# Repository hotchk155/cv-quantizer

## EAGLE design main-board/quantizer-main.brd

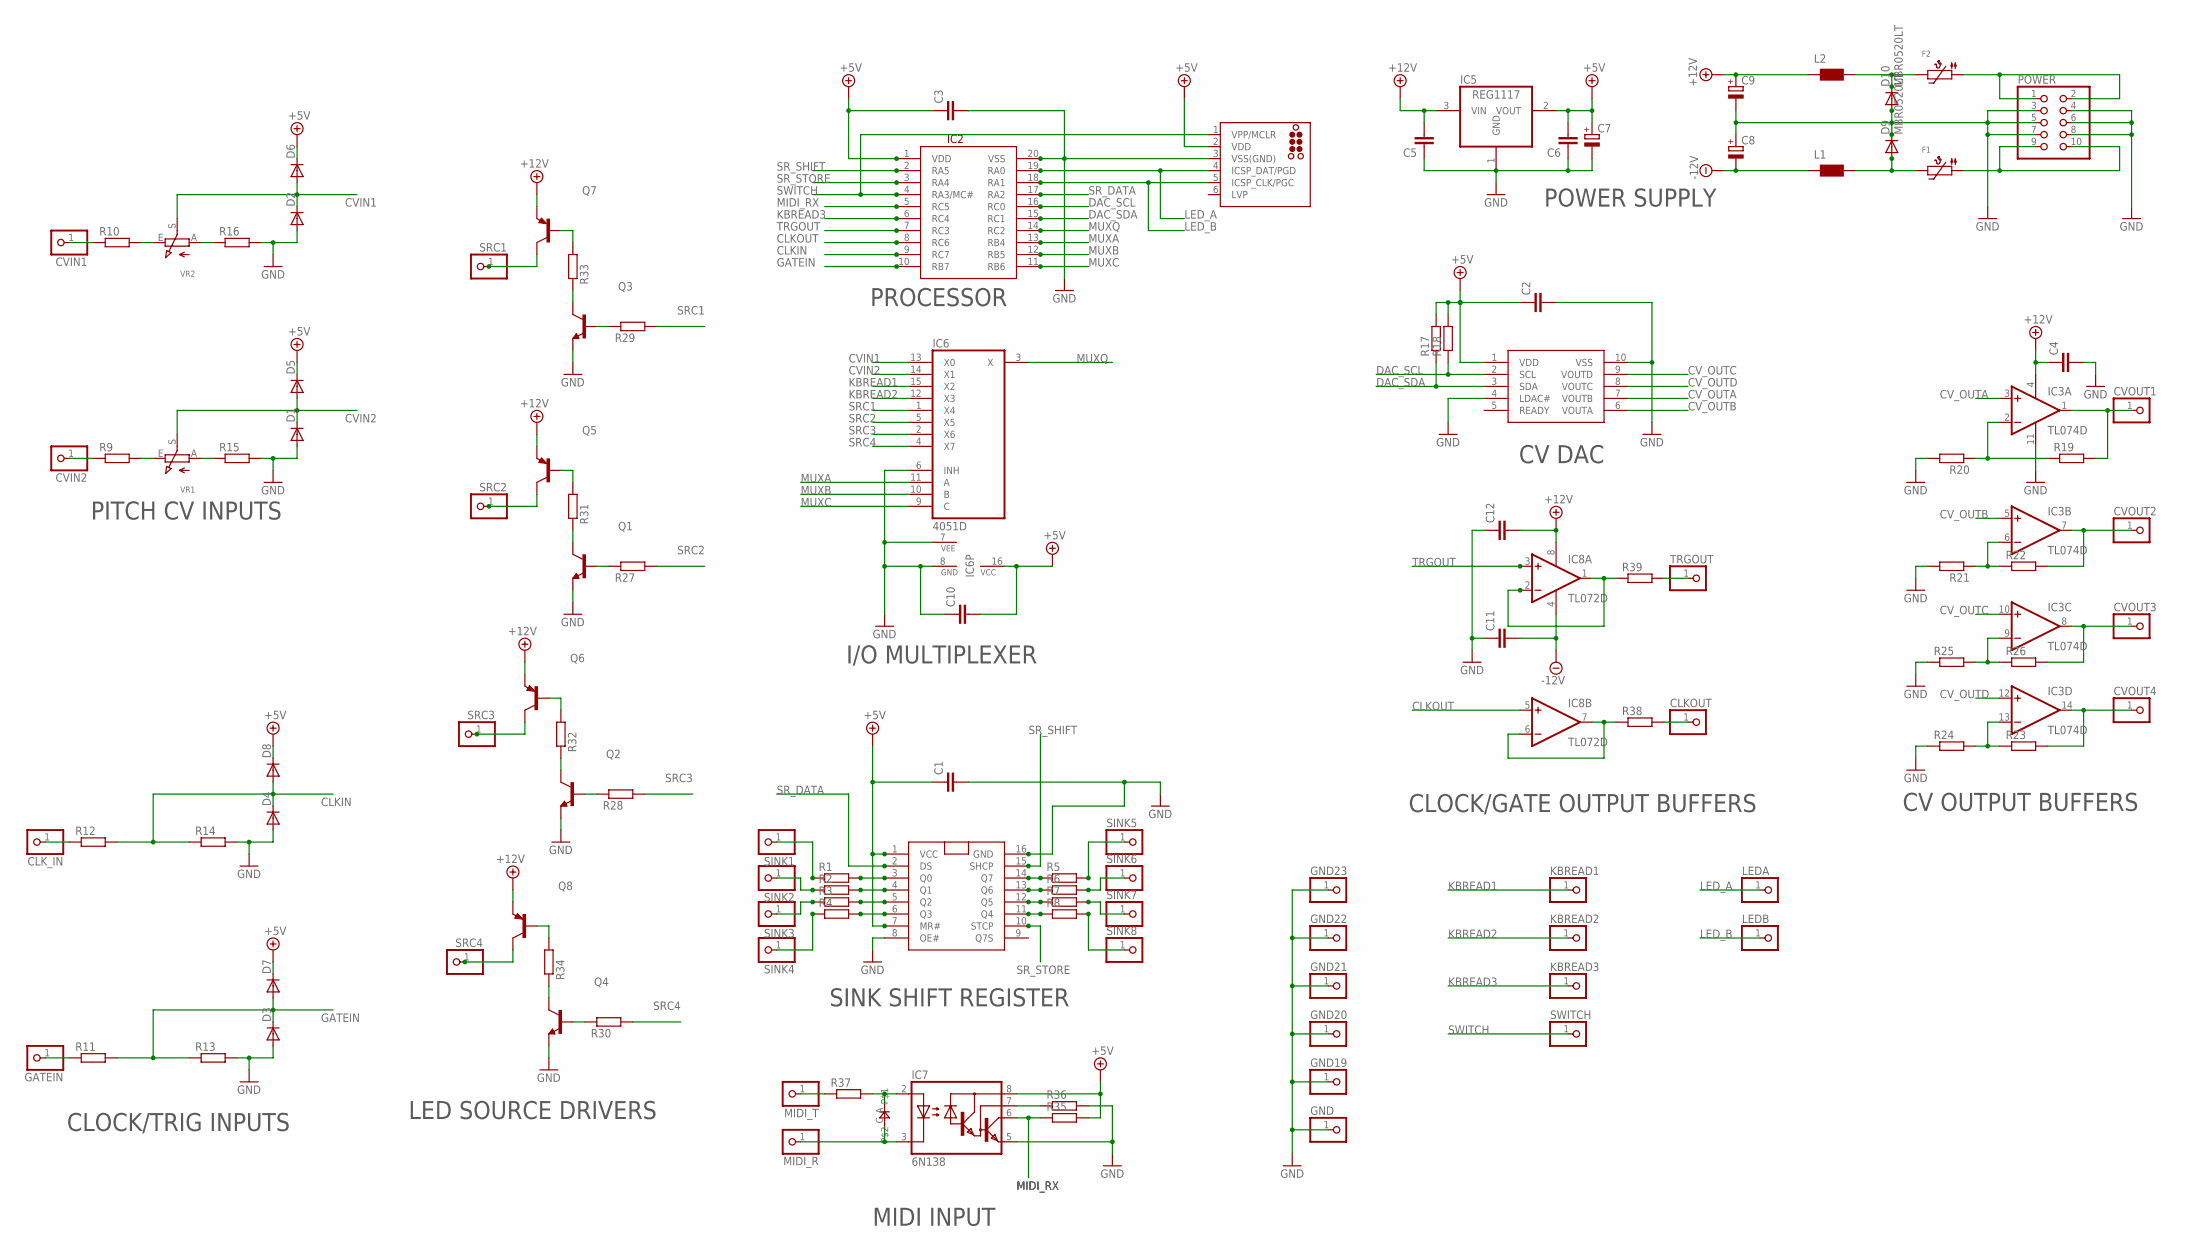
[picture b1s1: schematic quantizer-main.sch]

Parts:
C1, C2, C3, C4, C5, C6, C10, C11, C12: C-EUC0805; C0805
C7: CPOL-EUE2.5-5; E2,5-5
C8, C9: CPOL-EUE2.5-7; E2,5-7
CLKOUT: PINHD-1X1; 1X01
CLK_IN: PINHD-1X1; 1X01
CVIN1, CVIN2: PINHD-1X1; 1X01
CVOUT1, CVOUT2, CVOUT3, CVOUT4: PINHD-1X1; 1X01
D1, D2, D3, D4, D5, D6, D7, D8: DIODE-SOD123; SOD123
D9, D10: MBR0520LT; SOD123
D11: 0805DIODE
F1, F2: PTC1210
GATEIN: PINHD-1X1; 1X01
GND, GND19, GND20, GND21, GND22, GND23: PINHD-1X1; 1X01
IC1: NPIC6C596; SO16
IC2: PIC16F1829SOIC; SO20W
IC3: TL074D; SO14
IC4: MCP4728_QUAD_DAC; MSOP10
IC5: REG1117; SOT223
IC6: 4051D; SO16
IC7: 6N138; DIL08
IC8: TL072D; SO08
J1: TC2030-MCP-NL
KBREAD1, KBREAD2, KBREAD3: PINHD-1X1; 1X01
L1, L2: WE-CBF_0805; 0805
LEDA: PINHD-1X1; 1X01
LEDB: PINHD-1X1; 1X01
MIDI_R: PINHD-1X1; 1X01
MIDI_T: PINHD-1X1; 1X01
POWER: PINHD-2X5; 2X05
Q1, Q2, Q3, Q4: MMBT3904LT1-NPN-SOT23-BEC; SOT23-BEC
Q5, Q6, Q7, Q8: MMBT3906LT1-PNP-SOT23-BEC; SOT23-BEC
R1, R2, R3, R4, R5, R6, R7, R8, R9, R10, R11, R12, R13, R14, R15, R16, R17, R18, R19, R20, R21, R22, R23, R24, R25, R26, R27, R28, R29, R30, R31, R32, R33, R34, R35, R36, R37, R38, R39: R-EU_R0805; R0805
SINK1, SINK2, SINK3, SINK4, SINK5, SINK6, SINK7, SINK8: PINHD-1X1; 1X01
SRC1, SRC2, SRC3, SRC4: PINHD-1X1; 1X01
SWITCH: PINHD-1X1; 1X01
TRGOUT: PINHD-1X1; 1X01
VR1, VR2: TRIMPOT10K_BOURNS; TRIMPOT_BOURNS3MM

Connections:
+5V: C1.1, C2.1, C3.1, C6.2, C7.+, C10.2, D5.C, D6.C, D7.C, D8.C, IC1.1 (VCC), IC1.7 (MR#), IC2.1 (VDD), IC4.1 (VDD), IC5.2 (VOUT), IC6.16 (VCC), IC7.8 (VCC), J1.2 (VDD), R17.2, R18.2, R35.2
+12V: C4.1, C5.2, C9.+, C12.2, IC3.4 (V+), IC5.3 (VIN), IC8.8 (V+), L2.1, Q5.E, Q6.E, Q7.E, Q8.E
-12V: C8.-, C11.2, IC8.4 (V-), L1.1
CLKIN: D4.C, D8.A, IC2.9 (RC7), R12.2, R14.1
CLKOUT: IC2.8 (RC6), IC8.5 (+IN)
CVIN1: D2.C, D6.A, IC6.13 (X0), VR2.S
CVIN2: D1.C, D5.A, IC6.14 (X1), VR1.S
CV_OUTA: IC3.3 (+IN), IC4.7 (VOUTB)
CV_OUTB: IC3.5 (+IN), IC4.6 (VOUTA)
CV_OUTC: IC3.10 (+IN), IC4.9 (VOUTD)
CV_OUTD: IC3.12 (+IN), IC4.8 (VOUTC)
DAC_SCL: IC2.16 (RC0), IC4.2 (SCL), R18.1
DAC_SDA: IC2.15 (RC1), IC4.3 (SDA), R17.1
GATEIN: D3.C, D7.A, IC2.10 (RB7), R11.2, R13.1
GND: C1.2, C2.2, C3.2, C4.2, C5.1, C6.1, C7.-, C8.+, C9.-, C10.1, C11.1, C12.1, D1.A, D2.A, D3.A, D4.A, D9.C, D10.A, GND.1, GND19.1, GND20.1, GND21.1, GND22.1, GND23.1, IC1.8 (OE#), IC1.16 (GND), IC2.20 (VSS), IC3.11 (V-), IC4.4 (LDAC#), IC4.10 (VSS), IC5.1 (GND), IC6.6 (INH), IC6.7 (VEE), IC6.8 (GND), IC7.5 (GND), J1.3 (VSS(GND)), POWER.3, POWER.4, POWER.5, POWER.6, POWER.7, POWER.8, Q1.E, Q2.E, Q3.E, Q4.E, R13.2, R14.2, R15.2, R16.2, R20.2, R21.2, R24.1, R25.1, R36.2
KBREAD1: IC6.15 (X2), KBREAD1.1
KBREAD2: IC6.12 (X3), KBREAD2.1
KBREAD3: IC2.6 (RC4), KBREAD3.1
LED_A: IC2.19 (RA0), J1.4 (ICSP_DAT/PGD), LEDA.1
LED_B: IC2.18 (RA1), J1.5 (ICSP_CLK/PGC), LEDB.1
MIDI_RX: IC2.5 (RC5), IC7.6 (VO), R35.1
MUXA: IC2.13 (RB4), IC6.11 (A)
MUXB: IC2.12 (RB5), IC6.10 (B)
MUXC: IC2.11 (RB6), IC6.9 (C)
MUXQ: IC2.14 (RC2), IC6.3 (X)
unnamed: CVOUT1.1, IC3.1 (OUT), R19.2
unnamed: IC3.2 (-IN), R19.1, R20.1
unnamed: R1.1, SINK1.1
unnamed: IC3.6 (-IN), R21.1, R22.1
unnamed: CVOUT2.1, IC3.7 (OUT), R22.2
unnamed: R2.1, SINK2.1
unnamed: R3.1, SINK3.1
unnamed: R4.1, SINK4.1
unnamed: CVOUT3.1, IC3.8 (OUT), R26.2
unnamed: CVOUT4.1, IC3.14 (OUT), R23.2
unnamed: IC3.9 (-IN), R25.2, R26.1
unnamed: IC3.13 (-IN), R23.1, R24.2
unnamed: IC1.3 (Q0), R1.2
unnamed: IC1.4 (Q1), R2.2
unnamed: IC1.5 (Q2), R3.2
unnamed: IC1.6 (Q3), R4.2
unnamed: R5.2, SINK5.1
unnamed: R6.2, SINK6.1
unnamed: R7.2, SINK7.1
unnamed: R8.2, SINK8.1
unnamed: IC1.14 (Q7), R5.1
unnamed: IC1.13 (Q6), R6.1
unnamed: IC1.12 (Q5), R7.1
unnamed: IC1.11 (Q4), R8.1
unnamed: Q7.C, SRC1.1
unnamed: Q3.B, R29.1
unnamed: MIDI_T.1, R37.1
unnamed: Q7.B, R33.2
unnamed: Q5.C, SRC2.1
unnamed: Q1.B, R27.1
unnamed: D11.A, IC7.2 (A), R37.2
unnamed: Q3.C, R33.1
unnamed: Q5.B, R31.2
unnamed: Q1.C, R31.1
unnamed: D11.C, IC7.3 (C), MIDI_R.1
unnamed: Q6.C, SRC3.1
unnamed: Q2.B, R28.1
unnamed: Q6.B, R32.2
unnamed: Q2.C, R32.1
unnamed: Q8.C, SRC4.1
unnamed: D10.C, F2.P$2 (2), L2.2
unnamed: D9.A, F1.P$2 (2), L1.2
unnamed: Q4.B, R30.1
unnamed: Q8.B, R34.2
unnamed: CLK_IN.1, R12.1
unnamed: IC7.7 (VB), R36.1
unnamed: Q4.C, R34.1
unnamed: GATEIN.1, R11.1
unnamed: CVIN2.1, R9.1
unnamed: R9.2, VR1.E
unnamed: R15.1, VR1.A
unnamed: CVIN1.1, R10.1
unnamed: R10.2, VR2.E
unnamed: R16.1, VR2.A
unnamed: IC8.1 (OUT), IC8.2 (-IN), R39.1
unnamed: IC8.6 (-IN), IC8.7 (OUT), R38.1
unnamed: F1.P$1 (1), POWER.9, POWER.10
unnamed: R39.2, TRGOUT.1
unnamed: CLKOUT.1, R38.2
unnamed: F2.P$1 (1), POWER.1, POWER.2
SRC1: IC6.1 (X4), R29.2
SRC2: IC6.5 (X5), R27.2
SRC3: IC6.2 (X6), R28.2
SRC4: IC6.4 (X7), R30.2
SR_DATA: IC1.2 (DS), IC2.17 (RA2)
SR_SHIFT: IC1.15 (SHCP), IC2.2 (RA5)
SR_STORE: IC1.10 (STCP), IC2.3 (RA4)
SWITCH: IC2.4 (RA3/MC#), J1.1 (VPP/MCLR), SWITCH.1
TRGOUT: IC2.7 (RC3), IC8.3 (+IN)

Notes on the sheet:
MIDI INPUT
POWER SUPPLY
CV OUTPUT BUFFERS
CV DAC
CLOCK/GATE OUTPUT BUFFERS
PROCESSOR
I/O MULTIPLEXER
SINK SHIFT REGISTER
CLOCK/TRIG INPUTS
LED SOURCE DRIVERS
PITCH CV INPUTS

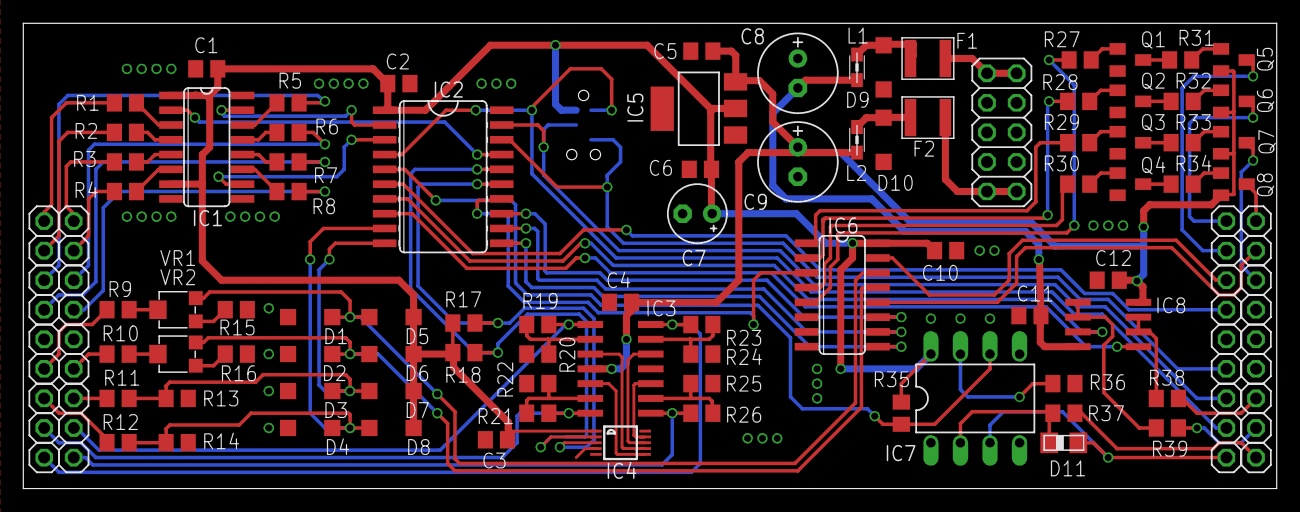
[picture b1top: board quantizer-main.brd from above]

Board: 2 copper layers, 107.7 x 40.0 mm, 122 parts (1 on the bottom side), 94 nets.

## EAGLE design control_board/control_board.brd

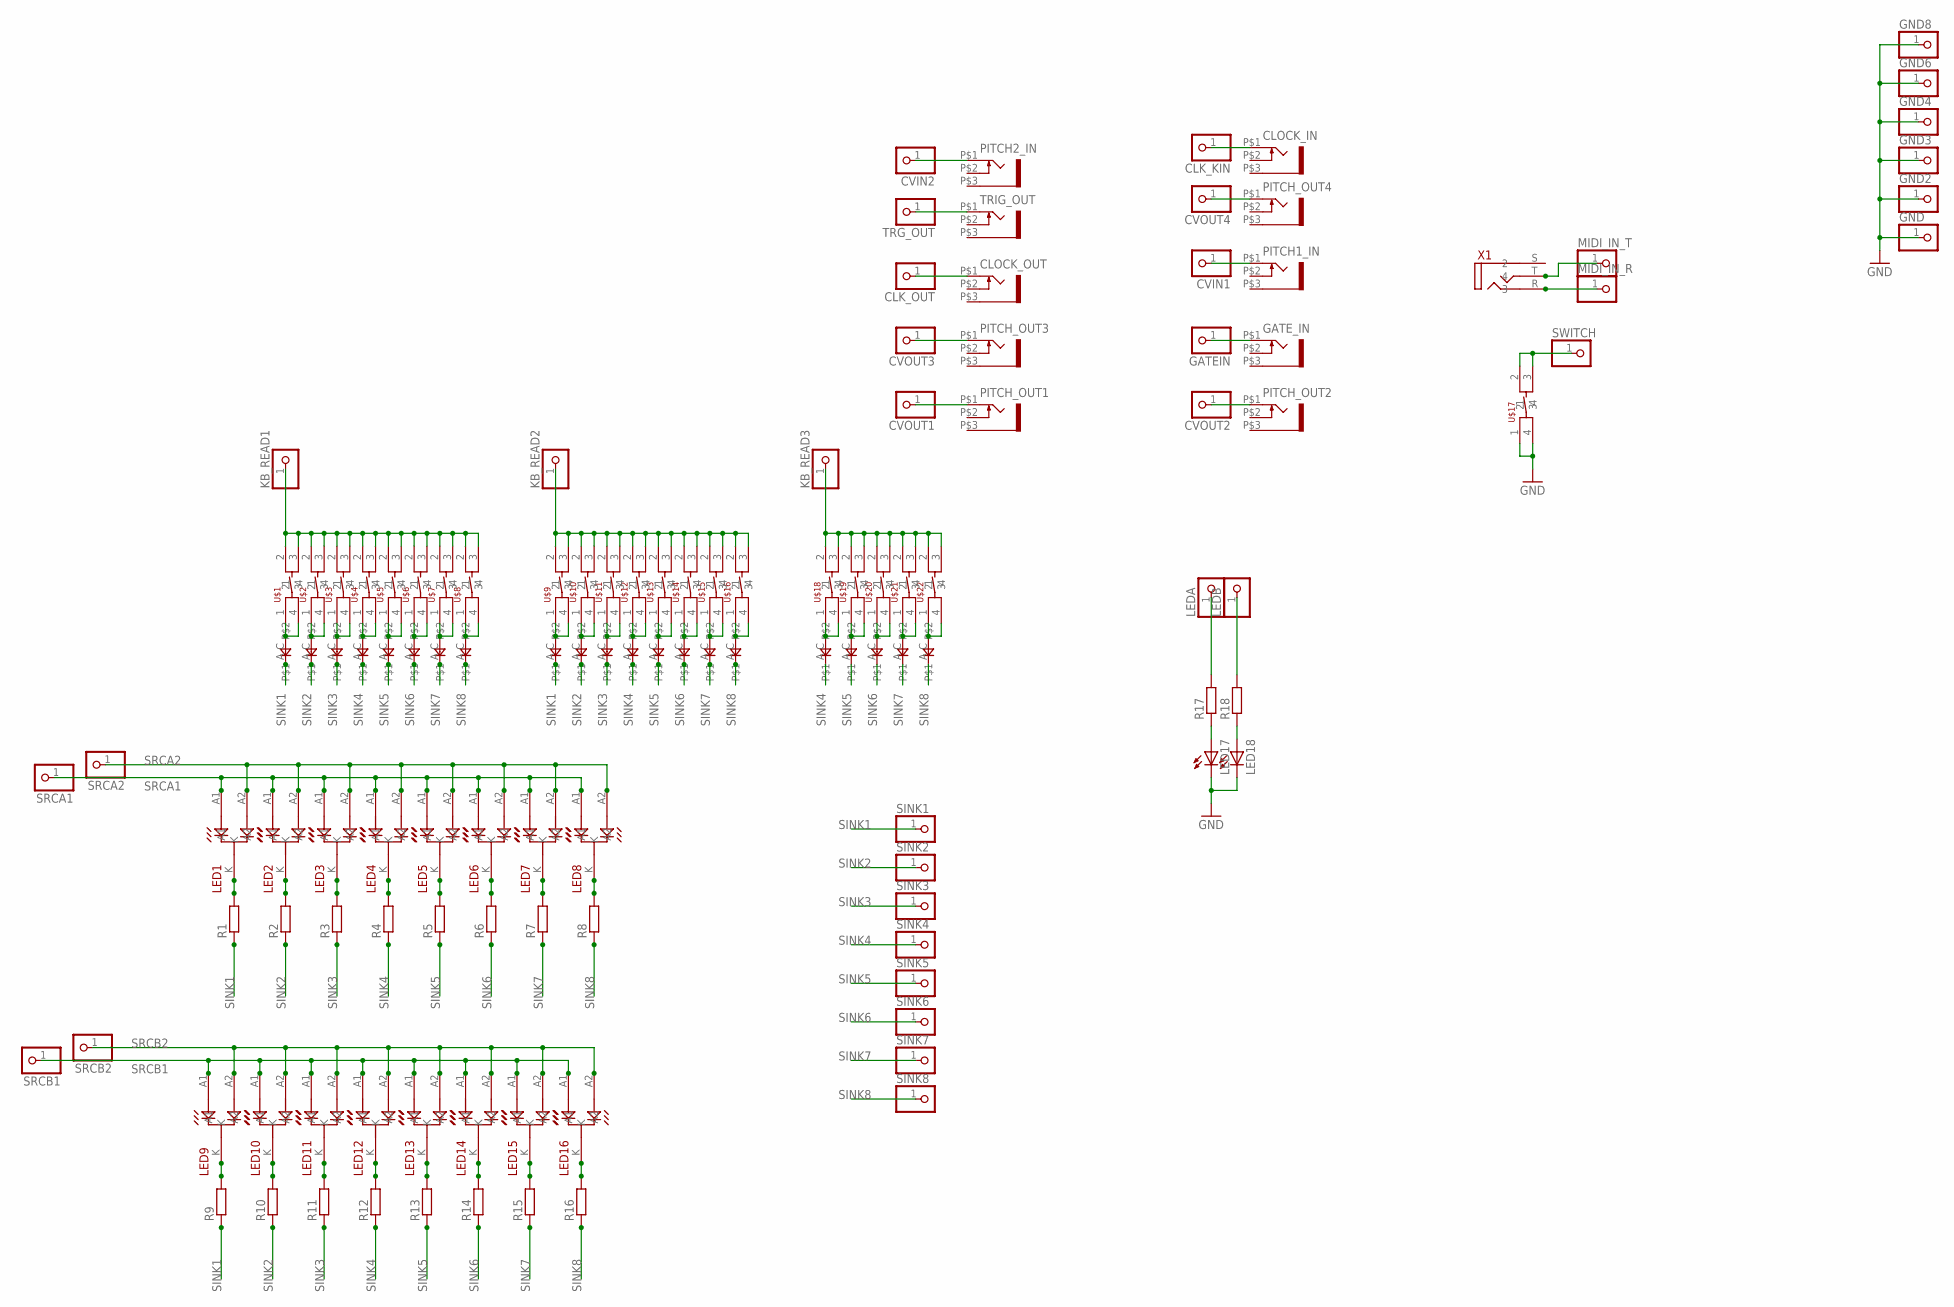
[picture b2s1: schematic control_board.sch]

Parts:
CLK_KIN: PINHD-1X1; 1X01
CLK_OUT: PINHD-1X1; 1X01
CLOCK_IN: WQP-PJ301M-12_JACK
CLOCK_OUT: WQP-PJ301M-12_JACK
CVIN1, CVIN2: PINHD-1X1; 1X01
CVOUT1, CVOUT2, CVOUT3, CVOUT4: PINHD-1X1; 1X01
GATEIN: PINHD-1X1; 1X01
GATE_IN: WQP-PJ301M-12_JACK
GND, GND2, GND3, GND4, GND6, GND8: PINHD-1X1; 1X01
KB_READ1, KB_READ2, KB_READ3: PINHD-1X1; 1X01
LED1, LED2, LED3, LED4, LED5, LED6, LED7, LED8, LED9, LED10, LED11, LED12, LED13, LED14, LED15, LED16: BICOL_LED_CC
LED17, LED18: LED3MM
LEDA: PINHD-1X1; 1X01
LEDB: PINHD-1X1; 1X01
MIDI_IN_R: PINHD-1X1; 1X01
MIDI_IN_T: PINHD-1X1; 1X01
PITCH1_IN, PITCH2_IN: WQP-PJ301M-12_JACK
PITCH_OUT1, PITCH_OUT2, PITCH_OUT3, PITCH_OUT4: WQP-PJ301M-12_JACK
R1, R2, R3, R4, R5, R6, R7, R8, R9, R10, R11, R12, R13, R14, R15, R16, R17, R18: R-EU_R0805; R0805
SINK1, SINK2, SINK3, SINK4, SINK5, SINK6, SINK7, SINK8: PINHD-1X1; 1X01
SRCA1, SRCA2: PINHD-1X1; 1X01
SRCB1, SRCB2: PINHD-1X1; 1X01
SWITCH: PINHD-1X1; 1X01
TRG_OUT: PINHD-1X1; 1X01
TRIG_OUT: WQP-PJ301M-12_JACK
U$1, U$2, U$3, U$4, U$5, U$6, U$7, U$8, U$9, U$10, U$11, U$12, U$13, U$14, U$15, U$16, U$17, U$18, U$19, U$20, U$21, U$22: 6MM_TACT; 6MMTACT
U$23, U$24, U$25, U$26, U$27, U$28, U$29, U$30, U$31, U$32, U$33, U$34, U$35, U$36, U$37, U$38, U$39, U$40, U$41, U$42, U$43: 0805DIODE
X1: VERTICAL_3_5MM_SOCKETTHONK; PJ301CM

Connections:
GND: GND.1, GND2.1, GND3.1, GND4.1, GND6.1, GND8.1, LED17.K (C), LED18.K (C), U$17.1, U$17.4
KB_READ: KB_READ2.1, U$9.2, U$9.3, U$10.2, U$10.3, U$11.2, U$11.3, U$12.2, U$12.3, U$13.2, U$13.3, U$14.2, U$14.3, U$15.2, U$15.3, U$16.2, U$16.3
LED2: LED2.K, R2.2
LEDA: LEDA.1, R17.2
unnamed: U$9.1, U$9.4, U$31.C
unnamed: KB_READ1.1, U$1.2, U$1.3, U$2.2, U$2.3, U$3.2, U$3.3, U$4.2, U$4.3, U$5.2, U$5.3, U$6.2, U$6.3, U$7.2, U$7.3, U$8.2, U$8.3
unnamed: U$10.1, U$10.4, U$32.C
unnamed: U$1.1, U$1.4, U$23.C
unnamed: U$2.1, U$2.4, U$24.C
unnamed: U$3.1, U$3.4, U$25.C
unnamed: U$4.1, U$4.4, U$26.C
unnamed: U$5.1, U$5.4, U$27.C
unnamed: U$18.1, U$18.4, U$39.C
unnamed: U$19.1, U$19.4, U$40.C
unnamed: U$20.1, U$20.4, U$41.C
unnamed: KB_READ3.1, U$18.2, U$18.3, U$19.2, U$19.3, U$20.2, U$20.3, U$21.2, U$21.3, U$22.2, U$22.3
unnamed: U$6.1, U$6.4, U$28.C
unnamed: U$11.1, U$11.4, U$33.C
unnamed: U$12.1, U$12.4, U$34.C
unnamed: U$13.1, U$13.4, U$35.C
unnamed: LED1.K, R1.2
unnamed: U$14.1, U$14.4, U$36.C
unnamed: LED17.A, R17.1
unnamed: LED3.K, R3.2
unnamed: LED4.K, R4.2
unnamed: LED5.K, R5.2
unnamed: LED6.K, R6.2
unnamed: LED7.K, R7.2
unnamed: LED8.K, R8.2
unnamed: U$16.1, U$16.4, U$38.C
unnamed: LED9.K, R9.2
unnamed: U$15.1, U$15.4, U$37.C
unnamed: LED10.K, R10.2
unnamed: LED11.K, R11.2
unnamed: LED12.K, R12.2
unnamed: LED13.K, R13.2
unnamed: LED14.K, R14.2
unnamed: LED15.K, R15.2
unnamed: LED16.K, R16.2
unnamed: LED18.A, R18.1
unnamed: MIDI_IN_R.1, X1.R (3)
unnamed: U$8.1, U$8.4, U$30.C
unnamed: U$7.1, U$7.4, U$29.C
unnamed: LEDB.1, R18.2
unnamed: U$22.1, U$22.4, U$43.C
unnamed: U$21.1, U$21.4, U$42.C
unnamed: SWITCH.1, U$17.2, U$17.3
unnamed: MIDI_IN_T.1, X1.T (4)
unnamed: CVIN2.1, PITCH2_IN.P$1 (2)
unnamed: TRG_OUT.1, TRIG_OUT.P$1 (2)
unnamed: CLK_OUT.1, CLOCK_OUT.P$1 (2)
unnamed: CVOUT3.1, PITCH_OUT3.P$1 (2)
unnamed: CVOUT1.1, PITCH_OUT1.P$1 (2)
unnamed: CLK_KIN.1, CLOCK_IN.P$1 (2)
unnamed: CVOUT4.1, PITCH_OUT4.P$1 (2)
unnamed: CVIN1.1, PITCH1_IN.P$1 (2)
unnamed: GATEIN.1, GATE_IN.P$1 (2)
unnamed: CVOUT2.1, PITCH_OUT2.P$1 (2)
SINK1: R1.1, R9.1, SINK1.1, U$23.A, U$31.A
SINK2: R2.1, R10.1, SINK2.1, U$24.A, U$32.A
SINK3: R3.1, R11.1, SINK3.1, U$25.A, U$33.A
SINK4: R4.1, R12.1, SINK4.1, U$26.A, U$34.A, U$39.A
SINK5: R5.1, R13.1, SINK5.1, U$27.A, U$35.A, U$40.A
SINK6: R6.1, R14.1, SINK6.1, U$28.A, U$36.A, U$41.A
SINK7: R7.1, R15.1, SINK7.1, U$29.A, U$37.A, U$42.A
SINK8: R8.1, R16.1, SINK8.1, U$30.A, U$38.A, U$43.A
SRCA1: LED1.A1, LED2.A1, LED3.A1, LED4.A1, LED5.A1, LED6.A1, LED7.A1, LED8.A1, SRCA1.1
SRCA2: LED1.A2, LED2.A2, LED3.A2, LED4.A2, LED5.A2, LED6.A2, LED7.A2, LED8.A2, SRCA2.1
SRCB1: LED9.A1, LED10.A1, LED11.A1, LED12.A1, LED13.A1, LED14.A1, LED15.A1, LED16.A1, SRCB1.1
SRCB2: LED9.A2, LED10.A2, LED11.A2, LED12.A2, LED13.A2, LED14.A2, LED15.A2, LED16.A2, SRCB2.1

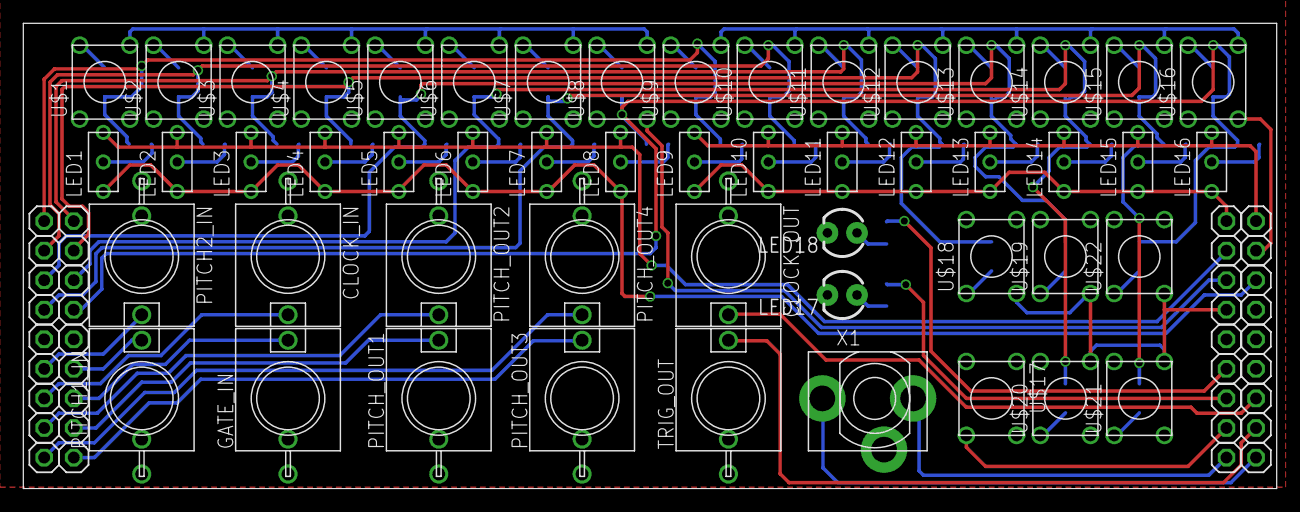
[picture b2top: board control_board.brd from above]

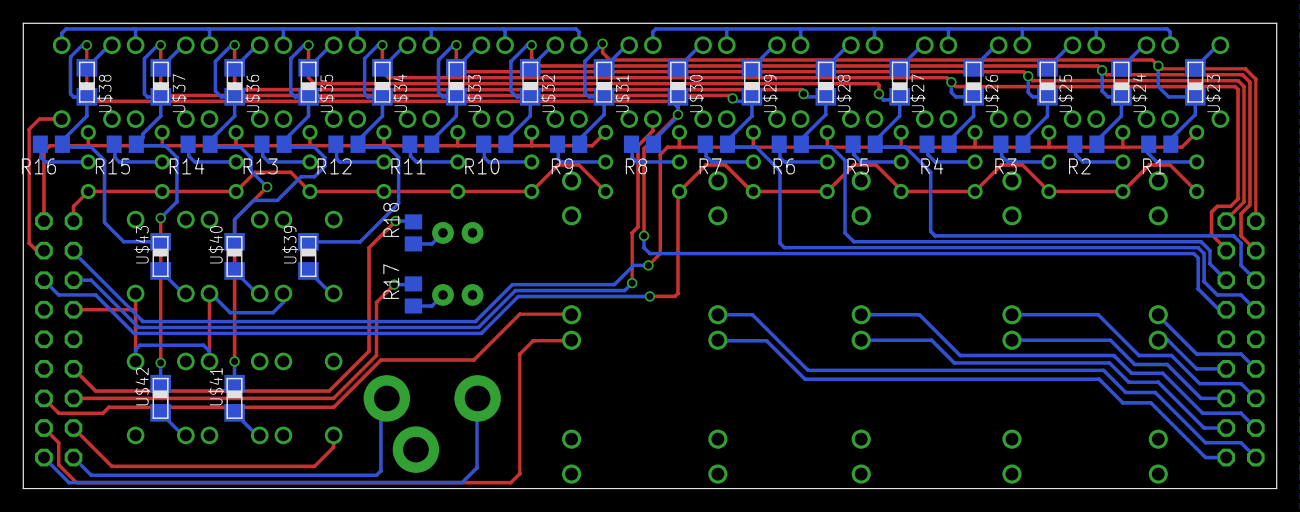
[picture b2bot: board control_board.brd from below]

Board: 2 copper layers, 107.7 x 40.0 mm, 126 parts (39 on the bottom side), 70 nets.

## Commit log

2017-09-04 :confetti_ball: Added .gitattributes & .gitignore files
2017-09-04 gdfgdf
2017-09-04 dsfds

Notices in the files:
parts and their libraries:
tag-connect: ©2009 ROFA.cz - modified and updated by Robert Darlington ‹rdarlington@gmail.com›
wuerth-elektronik: Copyright: Würth Elektronik eiSos
